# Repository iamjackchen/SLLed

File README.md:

# SLLed

A decorative lighting piece I designed and built for Valentine's day. The project is called "SLLed" because the intended recipient had supposedly caught me talking about singly-linked lists in my sleep.

Inspired by https://www.instructables.com/DIY-LED-heart/. 

</br>

## Hardware

I first started by building a schematic in KiCAD. Some design considerations:

 - I was at uni and didn't have access to my usual soldering equipment, so I had to get my PCB assembled by its manufacturer. This meant that my component selection was restricted to what the manufacturer had available. 

 - I also didn't have access to any mcu programming tools, so I wanted this module to be USB-programmable for ease of development. USB-C because, c'mon guys, it's 2023.

For the MCU I settled for the ATMega16U2, which is from the family of microcontrollers used in the classic Arduino line (the commonly-used 32U4 was out of stock). 

I added a 16MHZ crystal should I choose to implement some form of USB connectivity with a host device in the future (for which the 16U2's internal crystal would be insufficient).

I also designed a very simple MOSFET-based power-switching circuit so that this module can be powered both via battery and USB.
 
The final schematic may be found [here](https://github.com/iamjackchen/SLLed/blob/master/Hardware/schematic.pdf).

<br/>

I then assigned footprints to components and build a quick layout. Some design considerations:

 - For reasons of aesthetic purity, everything visible on the front-side of the PCB must be part of the heart. No vias outside of the heart!

 - Added a small hole to the top of the PCB, so you could thread a string through it and hang the module on somewhere

The geometry of the heart took some time to get right, but it turned out ok.

<br/>

I exported the Gerber files and BOM, and sent it off to JLCPCB for manufacture. Here are some renders: 

<br/>

## Software

In my humble opinion, using Arduino as a university student in _computer science_ is akin to intellectual cowardice. It is a sign that one lacks to bravery to face the almighty datasheet. /s

I programmed this in AVR C because I wanted to learn more about how microcontrollers worked at a lower level. Implementing I/O functions and interrupts by directly interacting with registers was a fun challenge and made the end result all the more rewarding. 

The [code](https://github.com/iamjackchen/SLLed/blob/master/Software/code.c) is structured as such:

 - I have system of decoding arrays so that the corresponding bits at the corresponding registers for each LED can be easily accessed via an index, where 0 is the top LED and the index moves through the heart clockwise.

 - The program runs on an infinite loop, which relies on a frame counter that increments and resets periodically. For each lighting mode, I have done some rudimentary maths to map the frame counter to the indices of the LEDs that need to be turned on or off.

 - An interrupt service routine is defined such that whenever the push-button (connected to Pin C2) is pressed, the loop resets and and the lighting mode changes.

There are currently 5 lighting modes built into the program : twinkle, heartbeat, vertical sweep, snake, and solid (hopefully these names are all self-explanatory).

<br/>

## Gallery

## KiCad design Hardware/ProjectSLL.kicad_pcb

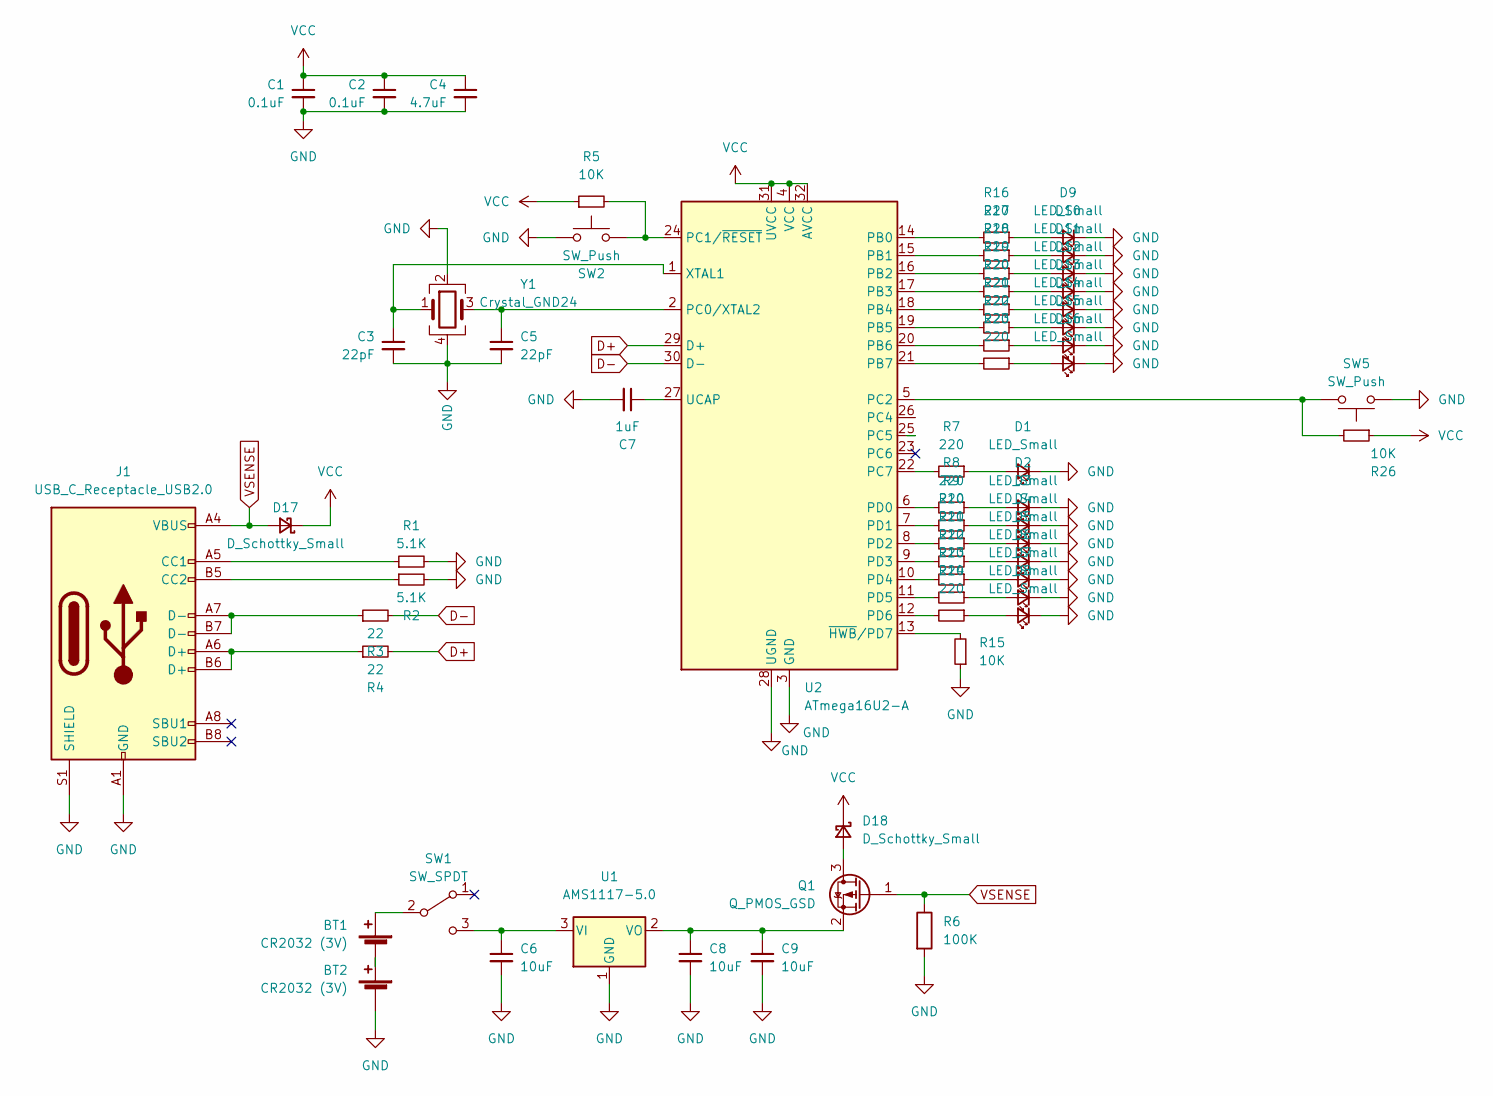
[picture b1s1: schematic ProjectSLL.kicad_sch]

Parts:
BT1, BT2: CR2032 (3V); BAT_CR2032-BS-6-1; LCSC C70377
C1, C2: 0.1uF; C_0603_1608Metric
C3, C5: 22pF; C_0603_1608Metric
C4: 4.7uF; C_0603_1608Metric
C6: 10uF; C_0603_1608Metric
C7: 1uF; C_0603_1608Metric
C8, C9: 10uF; CP_EIA-3216-18_Kemet-A; LCSC C7171
D1, D2, D3, D4, D5, D6, D7, D8, D9, D10, D11, D12, D13, D14, D15, D16: LED_Small; LED_0805_2012Metric
D17, D18: D_Schottky_Small; D_0603_1608Metric
J1: USB_C_Receptacle_USB2.0; USB_C_Receptacle_HRO_TYPE-C-31-M-12; LCSC C165948
Q1: Q_PMOS_GSD; SOT-23; LCSC C15127
R1, R2: 5.1K; R_0603_1608Metric
R3, R4: 22; R_0603_1608Metric
R5, R15, R26: 10K; R_0603_1608Metric
R6: 100K; R_0603_1608Metric
R7, R8, R9, R10, R11, R12, R13, R14, R16, R17, R18, R19, R20, R21, R22, R23: 220; R_0603_1608Metric
SW1: SW_SPDT; SW-SMD_MK-12C02-G020; LCSC C963206
SW2, SW5: SW_Push; SW_TS-1187A-B-A-B; LCSC C318884
U1: AMS1117-5.0; SOT-223-3_TabPin2; LCSC C6187
U2: ATmega16U2-A; TQFP-32_7x7mm_P0.8mm; LCSC C59019
Y1: Crystal_GND24; Crystal_SMD_3225-4Pin_3.2x2.5mm; LCSC C13738

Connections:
D+: R4.2, U2.29 (D+)
D-: R3.2, U2.30 (D-)
GND: BT2.2 (-), C1.2, C2.2, C3.2, C4.2, C5.2, C6.2, C7.2, C8.2, C9.2, D1.1 (K), D2.1 (K), D3.1 (K), D4.1 (K), D5.1 (K), D6.1 (K), D7.1 (K), D8.1 (K), D9.1 (K), D10.1 (K), D11.1 (K), D12.1 (K), D13.1 (K), D14.1 (K), D15.1 (K), D16.1 (K), J1.A1 (GND), J1.A12 (GND), J1.B1 (GND), J1.B12 (GND), J1.S1 (SHIELD), R1.2, R2.2, R6.2, R15.1, SW2.1, SW5.1, U1.1 (GND), U2.3 (GND), U2.28 (UGND), Y1.2, Y1.4
unnamed: BT1.1 (+), SW1.2 (B)
unnamed: BT1.2 (-), BT2.1 (+)
unnamed: C3.1, U2.1 (XTAL1), Y1.1
unnamed: C5.1, U2.2 (PC0/XTAL2), Y1.3
unnamed: C6.1, SW1.3 (C), U1.3 (VI)
unnamed: C7.1, U2.27 (UCAP)
unnamed: C8.1, C9.1, Q1.2 (S), U1.2 (VO)
unnamed: D1.2 (A), R7.1
unnamed: D2.2 (A), R8.1
unnamed: D3.2 (A), R9.1
unnamed: D4.2 (A), R10.1
unnamed: D5.2 (A), R11.1
unnamed: D6.2 (A), R12.1
unnamed: D7.2 (A), R13.1
unnamed: D8.2 (A), R14.1
unnamed: D9.2 (A), R16.1
unnamed: D10.2 (A), R17.1
unnamed: D11.2 (A), R18.1
unnamed: D12.2 (A), R19.1
unnamed: D13.2 (A), R20.1
unnamed: D14.2 (A), R21.1
unnamed: D15.2 (A), R22.1
unnamed: D16.2 (A), R23.1
unnamed: D18.2 (A), Q1.3 (D)
unnamed: J1.A5 (CC1), R1.1
unnamed: J1.A6 (D+), J1.B6 (D+), R4.1
unnamed: J1.A7 (D-), J1.B7 (D-), R3.1
unnamed: J1.B5 (CC2), R2.1
unnamed: R5.2, SW2.2, U2.24 (PC1/~RESET)
unnamed: R7.2, U2.22 (PC7)
unnamed: R8.2, U2.6 (PD0)
unnamed: R9.2, U2.7 (PD1)
unnamed: R10.2, U2.8 (PD2)
unnamed: R11.2, U2.9 (PD3)
unnamed: R12.2, U2.10 (PD4)
unnamed: R13.2, U2.11 (PD5)
unnamed: R14.2, U2.12 (PD6)
unnamed: R15.2, U2.13 (~HWB/PD7)
unnamed: R16.2, U2.14 (PB0)
unnamed: R17.2, U2.15 (PB1)
unnamed: R18.2, U2.16 (PB2)
unnamed: R19.2, U2.17 (PB3)
unnamed: R20.2, U2.18 (PB4)
unnamed: R21.2, U2.19 (PB5)
unnamed: R22.2, U2.20 (PB6)
unnamed: R23.2, U2.21 (PB7)
unnamed: R26.2, SW5.2, U2.5 (PC2)
VCC: C1.1, C2.1, C4.1, D17.1 (K), D18.1 (K), R5.1, R26.1, U2.4 (VCC), U2.31 (UVCC), U2.32 (AVCC)
VSENSE: D17.2 (A), J1.A4 (VBUS), J1.A9 (VBUS), J1.B4 (VBUS), J1.B9 (VBUS), Q1.1 (G), R6.1

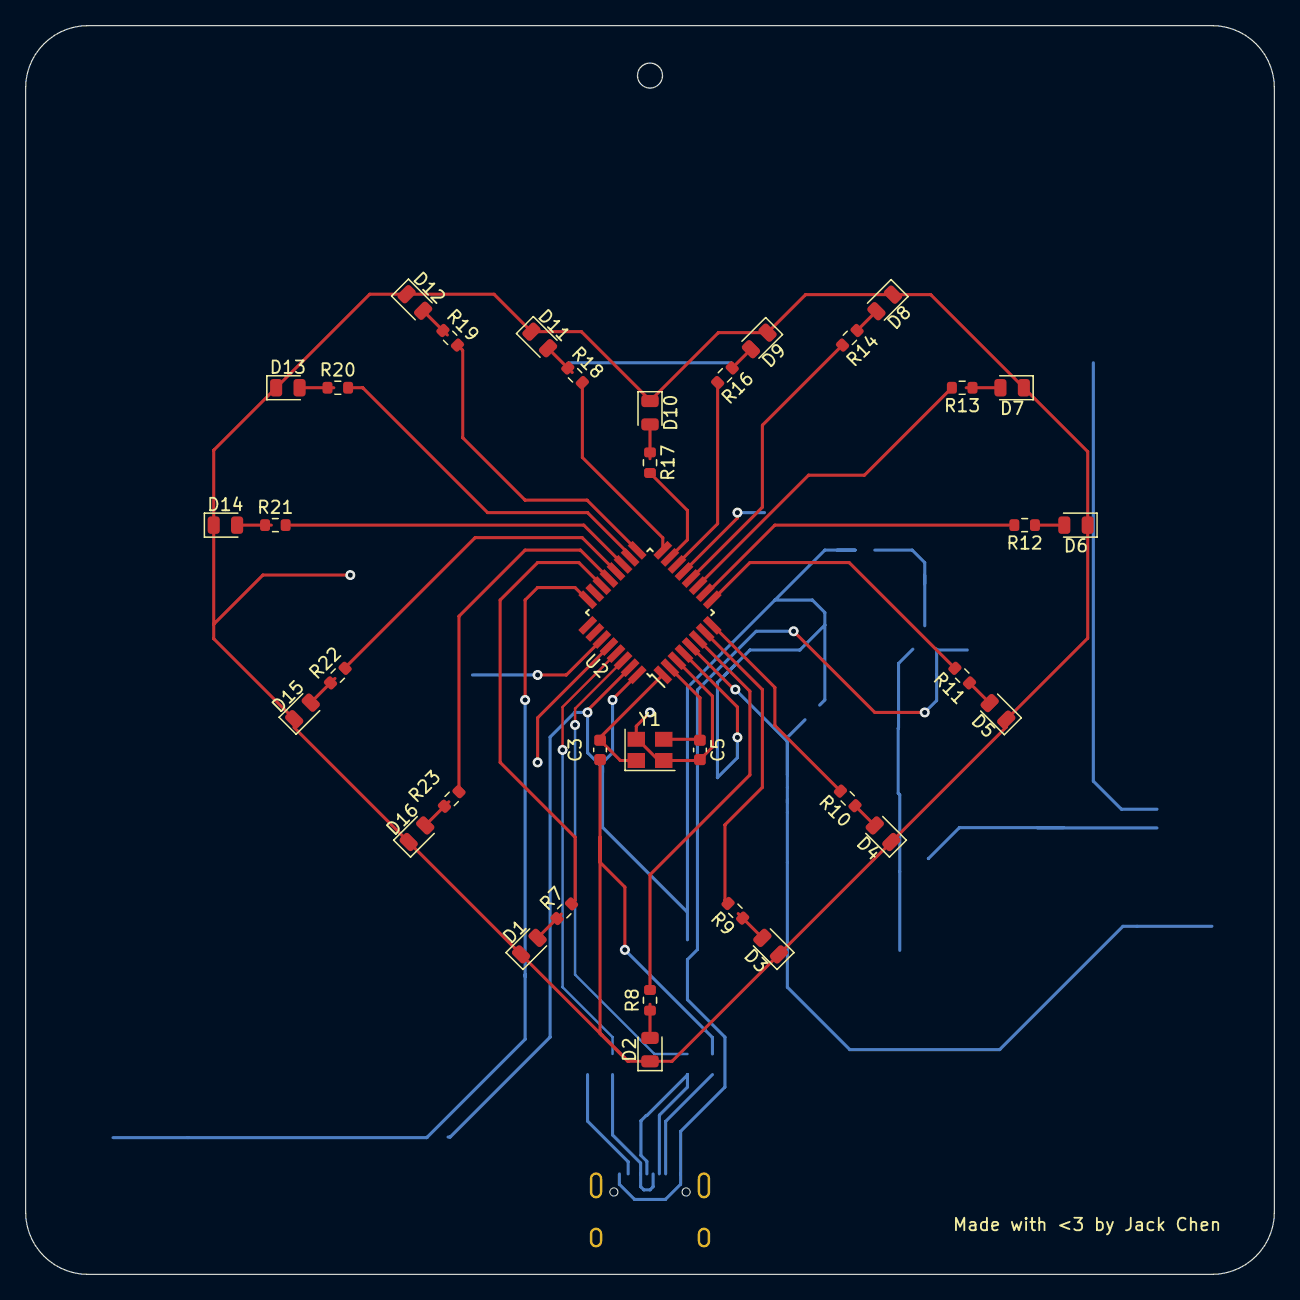
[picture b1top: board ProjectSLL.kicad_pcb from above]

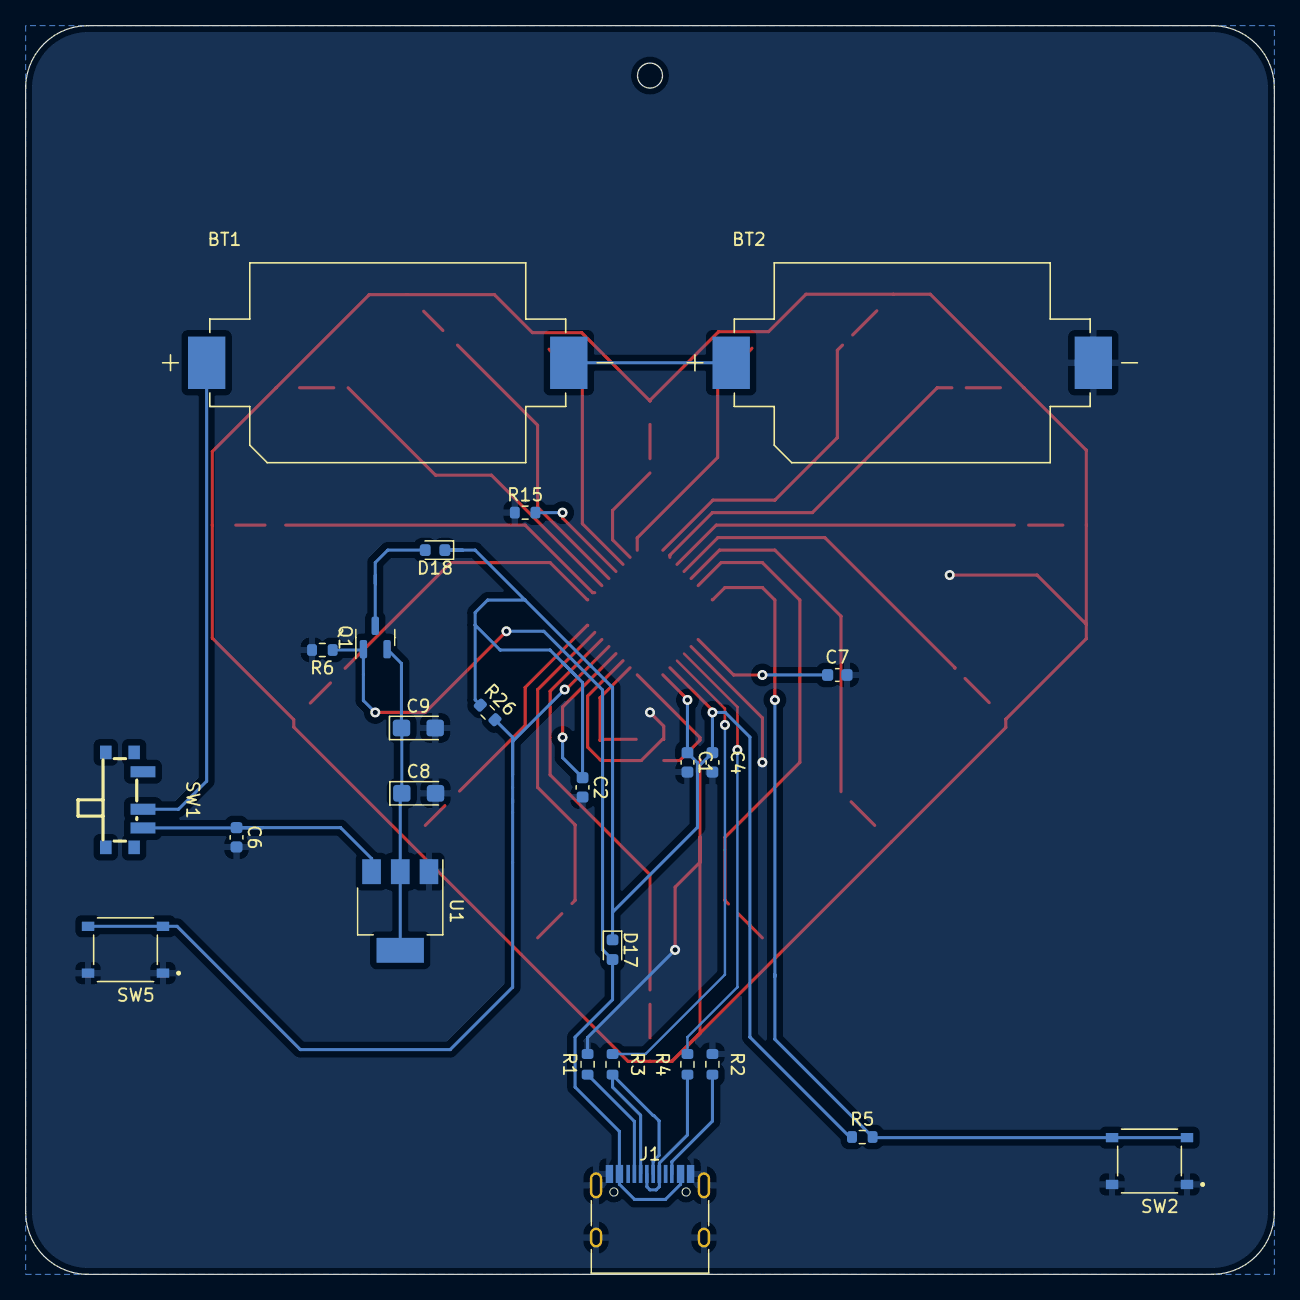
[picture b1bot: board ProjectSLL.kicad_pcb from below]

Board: 2 copper layers, 100.0 x 100.0 mm, 61 parts (25 on the bottom side), 52 nets.

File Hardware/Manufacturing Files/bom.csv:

Designator,Footprint,Quantity,Value,LCSC Part #
"BT1, BT2",BAT_CR2032-BS-6-1,2,CR2032 (3V),C70377
C1,0603,1,0.1uF,C15849
C2,0603,1,0.1uF,C15849
C3,0603,1,22pF,C1653
C4,0603,1,4.7uF,C19666
C5,0603,1,22pF,C1653
C6,0603,1,10uF,C19702
C7,0603,1,1uF,C15849
"C8, C9",CP_EIA-3216-18_Kemet-A,2,10uF,C7171
D1,0805,1,LED_Small,C84256
D10,0805,1,LED_Small,C84256
D11,0805,1,LED_Small,C84256
D12,0805,1,LED_Small,C84256
D13,0805,1,LED_Small,C84256
D14,0805,1,LED_Small,C84256
D15,0805,1,LED_Small,C84256
D16,0805,1,LED_Small,C84256
D2,0805,1,LED_Small,C84256
D3,0805,1,LED_Small,C84256
D4,0805,1,LED_Small,C84256
D5,0805,1,LED_Small,C84256
D6,0805,1,LED_Small,C84256
D7,0805,1,LED_Small,C84256
D8,0805,1,LED_Small,C84256
D9,0805,1,LED_Small,C84256
J1,USB_C_Receptacle_HRO_TYPE-C-31-M-12,1,USB_C_Receptacle_USB2.0,C165948
Q1,SOT-23,1,Q_PMOS_GSD,C15127
R1,0603,1,5.1K,C23186
R10,0603,1,220,C22962
R11,0603,1,220,C22962
R12,0603,1,220,C22962
R13,0603,1,220,C22962
R14,0603,1,220,C22962
R15,0603,1,10K,C25804
R16,0603,1,220,C22962
R17,0603,1,220,C22962
R18,0603,1,220,C22962
R19,0603,1,220,C22962
R2,0603,1,5.1K,C23186
R20,0603,1,220,C22962
R21,0603,1,220,C22962
R22,0603,1,220,C22962
R23,0603,1,220,C22962
R26,0603,1,10K,C25804
R3,0603,1,22,C23345
R4,0603,1,22,C23345
R5,0603,1,10K,C25804
R6,0603,1,100K,C25803
R7,0603,1,220,C22962
R8,0603,1,220,C22962
R9,0603,1,220,C22962
SW1,SW-SMD_MK-12C02-G020,1,SW_SPDT,C963206
"SW2, SW5",SW_TS-1187A-B-A-B,2,SW_Push,C318884
U1,SOT-223-3_TabPin2,1,AMS1117-5.0,C6187
U2,TQFP-32_7x7mm_P0.8mm,1,ATmega16U2-A,C59019
Y1,Crystal_SMD_3225-4Pin_3.2x2.5mm,1,Crystal_GND24,C13738

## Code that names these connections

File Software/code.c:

#define __AVR_ATmega16U2__

#include <avr/io.h> 
#include <avr/interrupt.h> 
#include <util/delay.h>

uint8_t counter = 0;
uint8_t mode = 0;

const uint8_t NUM_MODES = 5;


volatile uint8_t* ledmr[3] = {&DDRB, &DDRC, &DDRD};
volatile uint8_t* ledr[3] = {&PORTB, &PORTC, &PORTD};
const uint8_t conv[16] = {0, 0, 2, 2, 2, 2, 2, 2, 2, 1, 0, 0, 0, 0, 0, 0};

const uint8_t ledn[16] = {PB1, PB0, PD6, PD5, PD4, PD3, PD2, PD1, PD0, PC7, PB7, PB6, PB5, PB4, PB3, PB2};

void ledON(uint8_t index) { *(ledr[conv[index]]) |= (1 << ledn[index]); }
void ledOFF(uint8_t index) { *(ledr[conv[index]]) &= ~(1 << ledn[index]); }

void init_leds() {
    for (uint8_t i = 0; i < 16; i++) {
        *(ledmr[conv[i]]) |= (1 << ledn[i]);
        *(ledr[conv[i]]) &= ~(1 << ledn[i]);
    }
}

void allON() {
    for (uint8_t i = 0; i < 16; i++) {
        *(ledr[conv[i]]) |= (1 << ledn[i]);
    }
}

void allOFF() {
    for (uint8_t i = 0; i < 16; i++) {
        *(ledr[conv[i]]) &= ~(1 << ledn[i]);
    }
}


void init_interrupts()
{
    // Configure Pin C2 as input
    DDRC &= ~(1 << PC2);
    // Enable pull-up resistor on Pin C2
    PORTC |= (1 << PC2);

    // Enable interrupt on Pin C2 (PCINT11)
    PCICR |= (1 << PCIE1) | (1 << PCIE0); 
    PCMSK1 |= (1 << PCINT11); 
}

ISR(PCINT1_vect) {

    if (PINC & (1 << PC2)) {
        allOFF();

        mode = (mode+1) % NUM_MODES;
        counter = 0;

        if (mode == NUM_MODES - 1) {
            allON();
        }
    }

}

void startup() {

    // . .
    // . - . .  - - -    . . . -    . 
    // - . - -  - - -   . . -
    _delay_ms(100);

    allON();
    _delay_ms(25);
    allOFF();
    _delay_ms(25);
    allON();
    _delay_ms(25);
    allOFF();
    _delay_ms(25);

    _delay_ms(150);

    allON();
    _delay_ms(25);
    allOFF();
    _delay_ms(25);
    allON();
    _delay_ms(50);
    allOFF();
    _delay_ms(25);
    allON();
    _delay_ms(25);
    allOFF();
    _delay_ms(25);
    allON();
    _delay_ms(25);
    allOFF();
    _delay_ms(25);

    _delay_ms(75);

    allON();
    _delay_ms(50);
    allOFF();
    _delay_ms(25);
    allON();
    _delay_ms(50);
    allOFF();
    _delay_ms(25);
    allON();
    _delay_ms(50);
    allOFF();
    _delay_ms(25);

    _delay_ms(75);

    allON();
    _delay_ms(25);
    allOFF();
    _delay_ms(25);
    allON();
    _delay_ms(25);
    allOFF();
    _delay_ms(25);
    allON();
    _delay_ms(25);
    allOFF();
    _delay_ms(25);
    allON();
    _delay_ms(50);
    allOFF();
    _delay_ms(25);

    _delay_ms(75);

    allON();
    _delay_ms(25);
    allOFF();
    _delay_ms(25);

    _delay_ms(150);

    allON();
    _delay_ms(50);
    allOFF();
    _delay_ms(25);
    allON();
    _delay_ms(25);
    allOFF();
    _delay_ms(25);
    allON();
    _delay_ms(50);
    allOFF();
    _delay_ms(25);
    allON();
    _delay_ms(50);
    allOFF();
    _delay_ms(25);

    _delay_ms(75);

    allON();
    _delay_ms(50);
    allOFF();
    _delay_ms(25);
    allON();
    _delay_ms(50);
    allOFF();
    _delay_ms(25);
    allON();
    _delay_ms(50);
    allOFF();
    _delay_ms(25);

    _delay_ms(75);

    allON();
    _delay_ms(25);
    allOFF();
    _delay_ms(25);
    allON();
    _delay_ms(25);
    allOFF();
    _delay_ms(25);
    allON();
    _delay_ms(50);
    allOFF();
    _delay_ms(25);

    _delay_ms(75);


}

int main()
{

    init_leds();
    init_interrupts();

    startup();

    sei(); //Enable global interrupts


    while (1) {

        if (mode == 0) {
            counter = counter%8;
            if (counter%4 == 0) { //twinkle1
                for (uint8_t i = 0; i < 16; i+=2) {
                    ledON(i);
                }

                for (uint8_t i = 1; i < 16; i+=2) {
                    ledOFF(i);
                }

            } else if (counter%2 == 0) { //twinkle2-- "else if" very important so that twinkle2 is not triggered after twinkle1
                for (uint8_t i = 0; i < 16; i+=2) {
                    ledOFF(i);
                }

                for (uint8_t i = 1; i < 16; i+=2) {
                    ledON(i);
                }
            }

        } else if (mode == 1) {
            counter = counter%10;
            if (counter == 0 || counter == 2) {
                allON();
            } else if (counter == 1 || counter == 3) {
                allOFF();
            }

        } else if (mode == 2) {
            counter = counter%18;
            if (counter < 9) {
                if(counter != 8)
                    ledON(8+counter);
                ledON(8-counter);
            } else {
                if(counter != 17)
                    ledOFF(8+(counter-9));
                ledOFF(8-(counter-9));
            }
            
        } else if (mode == 3) {
            counter = counter%32;
            if (counter < 16)
                ledON(counter);
            else
                ledOFF(counter-16);
            
        } else if (mode == 4) {
            //do nothing
        }


        counter++;
        _delay_ms(25);

    }

    return 0;
}



/* LED Mappings (Clockwise, starting from top)
17  B1
16  B0
14  D6
13  D5
12  D4
11  D3
10  D2
09  D1
08  D0
07  C7
23  B7
22  B6
21  B5
20  B4
19  B3
18  B2
*/

/* MODES
0 - twinkle
1 - heart beat
2 - vertical snake
3 - snake
4 - solid

*/

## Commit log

2023-03-22 init commit 2
2023-03-22 edited images
2023-03-23 added photos
2023-03-23 updated images
2023-03-23 updated graphics
